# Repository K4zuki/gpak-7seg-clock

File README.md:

# gpak-7seg-clock
7-seg LED clock application using GreenPAK

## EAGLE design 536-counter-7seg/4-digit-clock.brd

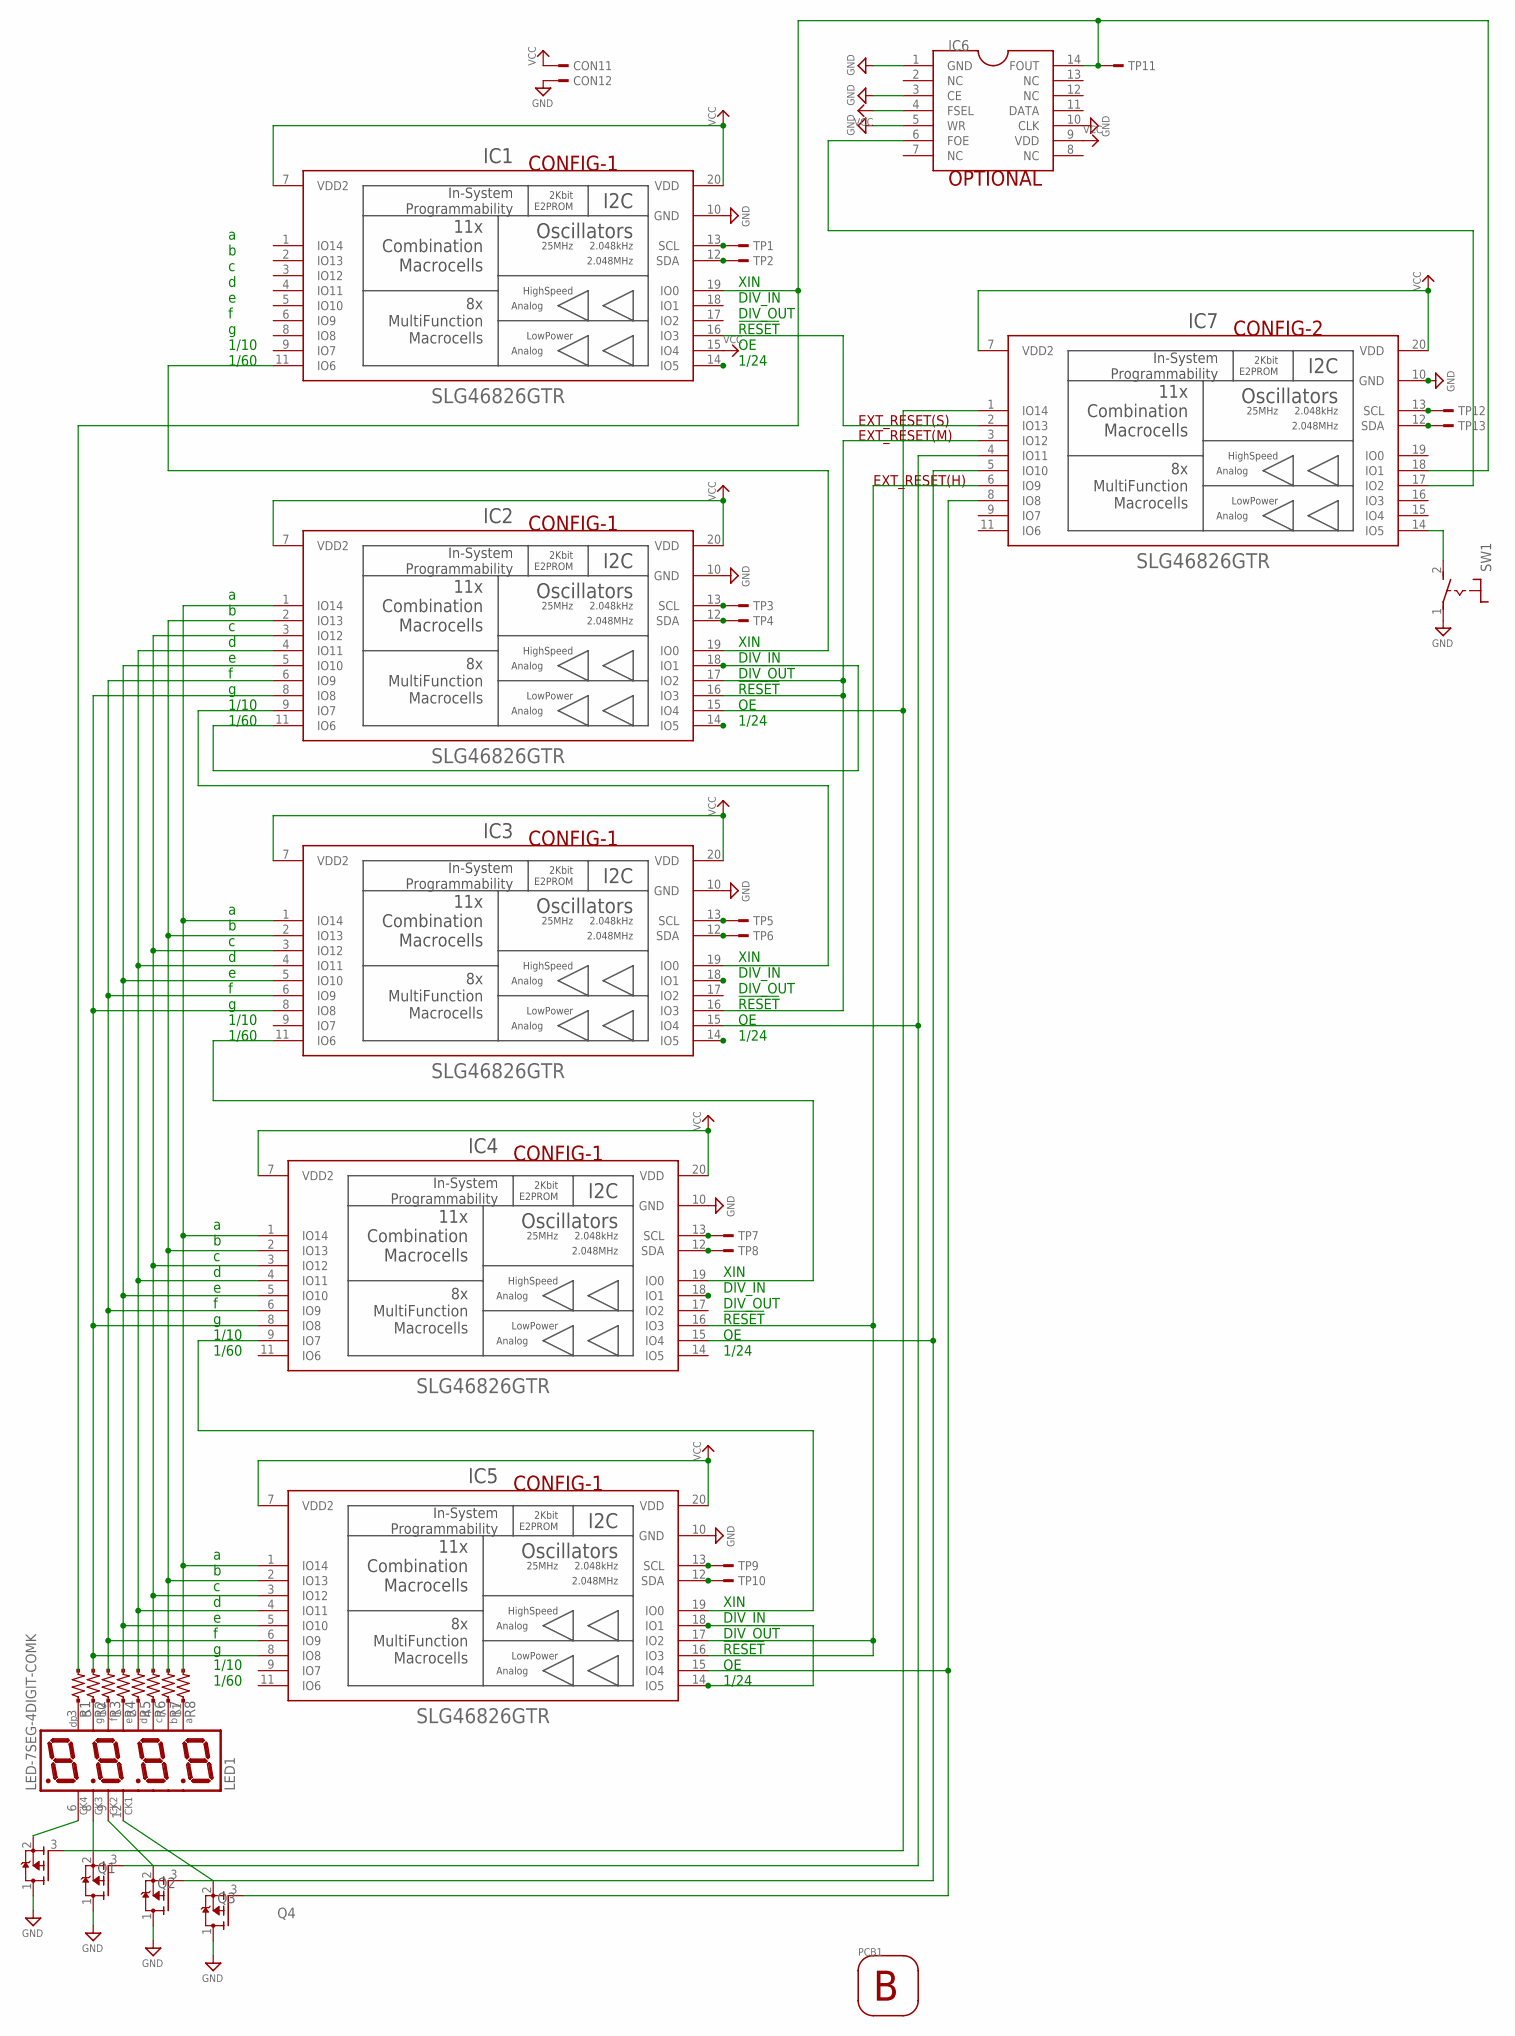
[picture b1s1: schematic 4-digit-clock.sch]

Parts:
CON1: B2B-XH-A; B2B-XH-A(LF)(SN)
IC1, IC2, IC3, IC4, IC5, IC7: SLG46826GTR; SOT65P650X440-20N
IC6: RTC-4543SA; SOT127P1010X500-14N
LED1: LED-7SEG-4DIGIT-COMK; LED-7SEG-4DIGIT
PCB1: P-MCS78A
Q1, Q2, Q3, Q4: 2N7002; SOT95P300X140-3N
R1, R2, R3, R4, R5, R6, R7, R8: R-US-1.0K-1005; C0402
SW1: TACTSW2-BK-TL1105S; SW-TACTSW-TL1105S
TP1, TP2, TP3, TP4, TP5, TP6, TP7, TP8, TP9, TP10, TP11, TP12, TP13: TESTPAD-1608; TP-1608

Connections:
GND: CON1.2, IC1.10 (GND), IC2.10 (GND), IC3.10 (GND), IC4.10 (GND), IC5.10 (GND), IC6.1 (GND), IC6.3 (CE), IC6.5 (WR), IC6.10 (CLK), IC7.10 (GND), Q1.1 (D), Q2.1 (D), Q3.1 (D), Q4.1 (D), SW1.1
unnamed: IC2.6 (IO9), IC3.6 (IO9), IC4.6 (IO9), IC5.6 (IO9), R3.2
unnamed: IC2.4 (IO11), IC3.4 (IO11), IC4.4 (IO11), IC5.4 (IO11), R5.2
unnamed: IC2.2 (IO13), IC3.2 (IO13), IC4.2 (IO13), IC5.2 (IO13), R7.2
unnamed: IC2.1 (IO14), IC3.1 (IO14), IC4.1 (IO14), IC5.1 (IO14), R8.2
unnamed: IC2.3 (IO12), IC3.3 (IO12), IC4.3 (IO12), IC5.3 (IO12), R6.2
unnamed: IC2.5 (IO10), IC3.5 (IO10), IC4.5 (IO10), IC5.5 (IO10), R4.2
unnamed: IC2.8 (IO8), IC3.8 (IO8), IC4.8 (IO8), IC5.8 (IO8), R2.2
unnamed: LED1.6 (CA4), Q1.2 (S)
unnamed: IC1.11 (IO6), IC2.19 (IO0)
unnamed: IC1.19 (IO0), IC6.14 (FOUT), IC7.18 (IO1), R1.2, TP11.TP
unnamed: IC2.11 (IO6), IC2.18 (IO1)
unnamed: LED1.8 (CA), Q2.2 (S)
unnamed: LED1.9 (CA), Q3.2 (S)
unnamed: LED1.12 (CA), Q4.2 (S)
unnamed: IC2.15 (IO4), IC7.1 (IO14), Q1.3 (G)
unnamed: IC3.15 (IO4), IC7.4 (IO11), Q2.3 (G)
unnamed: IC4.15 (IO4), IC7.5 (IO10), Q3.3 (G)
unnamed: IC2.9 (IO7), IC3.19 (IO0)
unnamed: IC5.15 (IO4), IC7.8 (IO8), Q4.3 (G)
unnamed: LED1.3 (DP), R1.1
unnamed: IC2.16 (IO3), IC2.17 (IO2), IC3.16 (IO3), IC7.3 (IO12)
unnamed: IC4.16 (IO3), IC5.16 (IO3), IC5.17 (IO2), IC7.6 (IO9)
unnamed: IC3.11 (IO6), IC4.19 (IO0)
unnamed: IC2.13 (SCL), TP3.TP
unnamed: IC2.12 (SDA), TP4.TP
unnamed: IC3.13 (SCL), TP5.TP
unnamed: IC3.12 (SDA), TP6.TP
unnamed: IC4.13 (SCL), TP7.TP
unnamed: IC4.12 (SDA), TP8.TP
unnamed: IC5.13 (SCL), TP9.TP
unnamed: IC5.14 (IO5), IC5.18 (IO1)
unnamed: LED1.5 (G), R2.1
unnamed: IC4.9 (IO7), IC5.19 (IO0)
unnamed: IC5.12 (SDA), TP10.TP
unnamed: LED1.10 (F), R3.1
unnamed: LED1.1 (E), R4.1
unnamed: LED1.2 (D), R5.1
unnamed: LED1.4 (C), R6.1
unnamed: LED1.7 (B), R7.1
unnamed: LED1.11 (A), R8.1
unnamed: IC7.13 (SCL), TP12.TP
unnamed: IC7.12 (SDA), TP13.TP
unnamed: IC7.14 (IO5), SW1.2 (S)
unnamed: IC6.6 (FOE), IC7.17 (IO2)
unnamed: IC1.16 (IO3), IC7.2 (IO13)
unnamed: IC1.13 (SCL), TP1.TP
unnamed: IC1.12 (SDA), TP2.TP
VCC: CON1.1, IC1.7 (VDD2), IC1.15 (IO4), IC1.20 (VDD), IC2.7 (VDD2), IC2.20 (VDD), IC3.7 (VDD2), IC3.20 (VDD), IC4.7 (VDD2), IC4.20 (VDD), IC5.7 (VDD2), IC5.20 (VDD), IC6.4 (FSEL), IC6.9 (VDD), IC7.7 (VDD2), IC7.20 (VDD)

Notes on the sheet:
XIN DIV_IN DIV_OUT !RESET! OE 1/24
a b c d e f g 1/10 1/60
CONFIG-1
CONFIG-2
OPTIONAL
EXT_RESET(S)
EXT_RESET(M)
EXT_RESET(H)

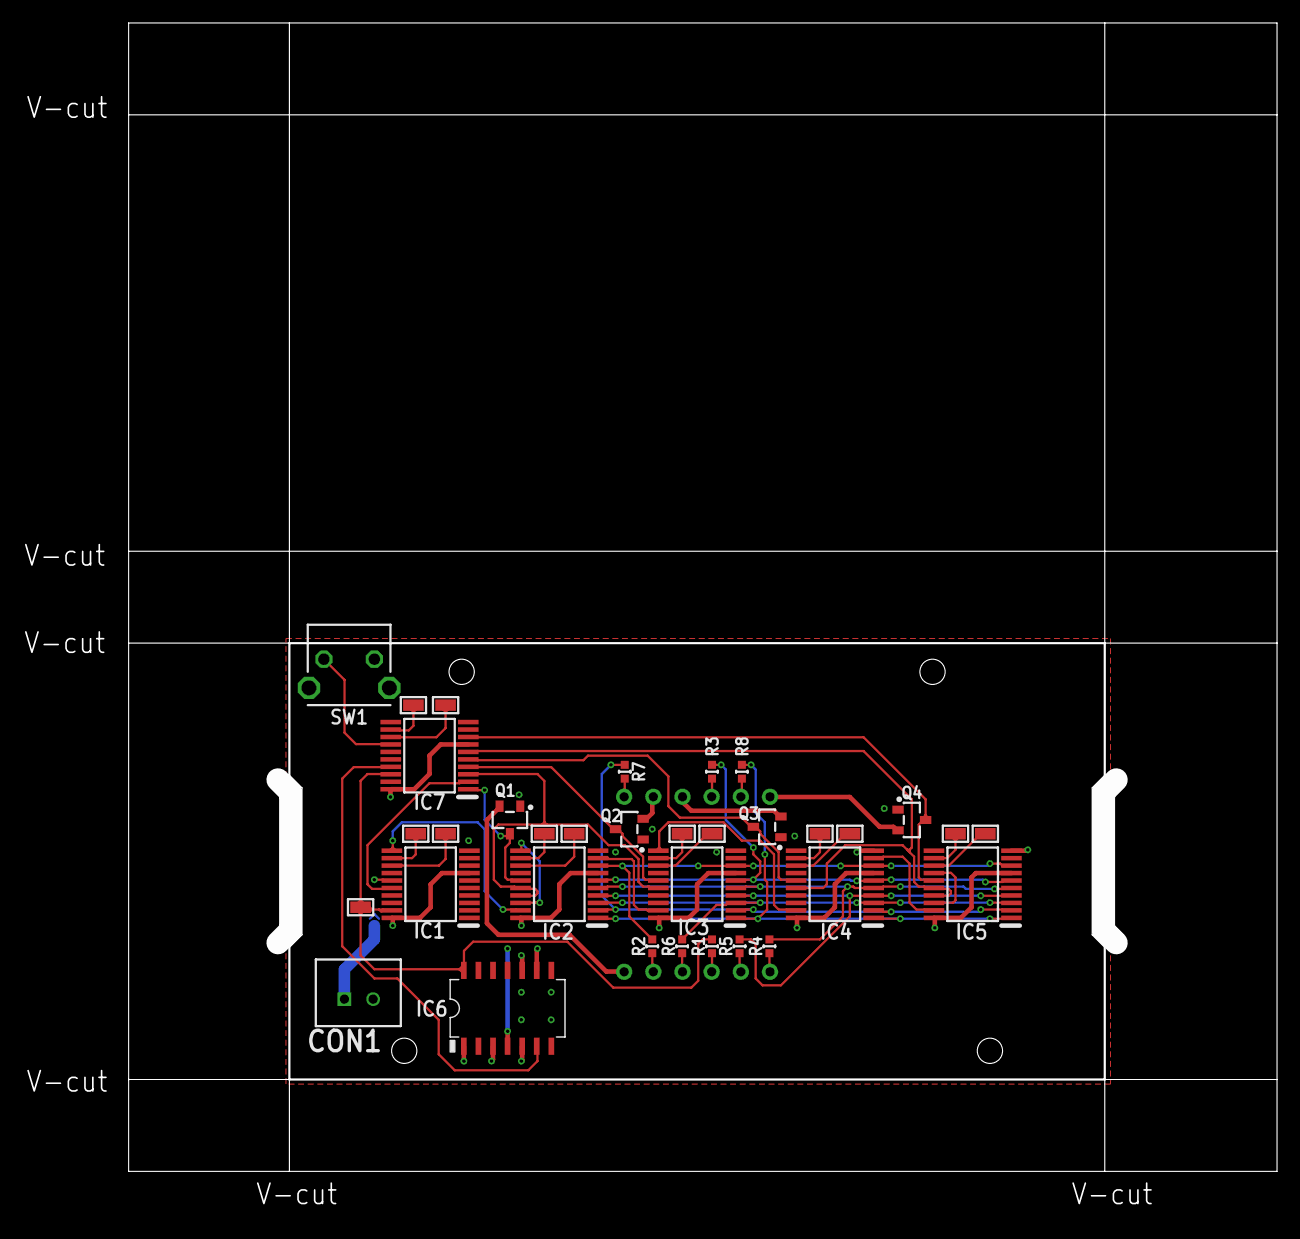
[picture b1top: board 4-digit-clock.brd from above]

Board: 2 copper layers, 107.2 x 101.9 mm, 36 parts (1 on the bottom side), 49 nets.

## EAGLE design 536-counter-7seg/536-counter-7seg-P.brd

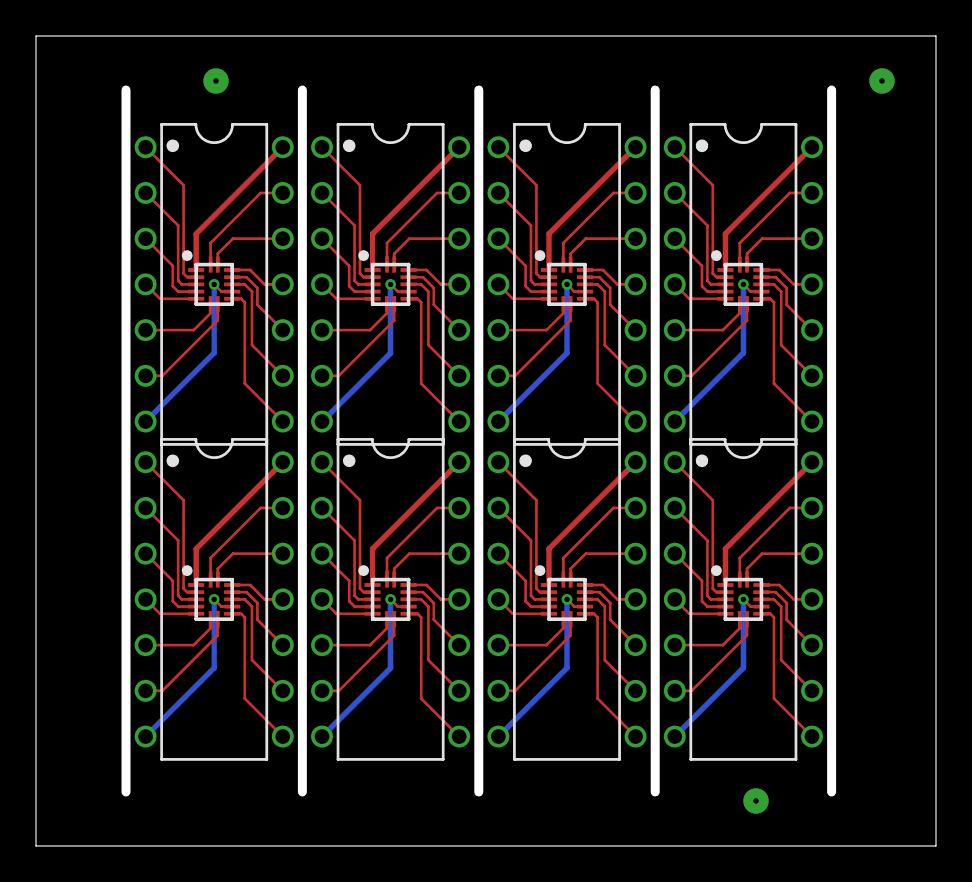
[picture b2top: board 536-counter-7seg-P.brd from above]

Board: 2 copper layers, 49.5 x 44.5 mm, 16 parts (0 on the bottom side), 112 nets.

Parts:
IC1, IC3, IC5, IC7, IC9, IC11, IC13, IC15: STQFN14-0.4P2.0X2.2
IC2, IC4, IC6, IC8, IC10, IC12, IC14, IC16: IC-TTL-74-04,14-DIP; IC-SOCKET-DIL-14

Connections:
GND: IC1.9, IC2.7
GND1: IC3.9, IC4.7
GND2: IC5.9, IC6.7
GND3: IC7.9, IC8.7
GND4: IC9.9, IC10.7
GND5: IC11.9, IC12.7
GND6: IC13.9, IC14.7
GND7: IC15.9, IC16.7
unnamed: IC1.1, IC2.14
unnamed: IC1.2, IC2.1
unnamed: IC1.3, IC2.2
unnamed: IC1.4, IC2.3
unnamed: IC1.5, IC2.4
unnamed: IC1.6, IC2.5
unnamed: IC1.7, IC2.6
unnamed: IC1.8, IC2.8
unnamed: IC1.10, IC2.9
unnamed: IC1.11, IC2.10
unnamed: IC1.12, IC2.11
unnamed: IC1.13, IC2.12
unnamed: IC1.14, IC2.13
unnamed: IC3.1, IC4.14
unnamed: IC3.2, IC4.1
unnamed: IC3.3, IC4.2
unnamed: IC3.4, IC4.3
unnamed: IC3.5, IC4.4
unnamed: IC3.6, IC4.5
unnamed: IC3.7, IC4.6
unnamed: IC3.8, IC4.8
unnamed: IC3.10, IC4.9
unnamed: IC3.11, IC4.10
unnamed: IC3.12, IC4.11
unnamed: IC3.13, IC4.12
unnamed: IC3.14, IC4.13
unnamed: IC5.1, IC6.14
unnamed: IC5.2, IC6.1
unnamed: IC5.3, IC6.2
unnamed: IC5.4, IC6.3
unnamed: IC5.5, IC6.4
unnamed: IC5.6, IC6.5
unnamed: IC5.7, IC6.6
unnamed: IC5.8, IC6.8
unnamed: IC5.10, IC6.9
unnamed: IC5.11, IC6.10
unnamed: IC5.12, IC6.11
unnamed: IC5.13, IC6.12
unnamed: IC5.14, IC6.13
unnamed: IC7.1, IC8.14
unnamed: IC7.2, IC8.1
unnamed: IC7.3, IC8.2
unnamed: IC7.4, IC8.3
unnamed: IC7.5, IC8.4
unnamed: IC7.6, IC8.5
unnamed: IC7.7, IC8.6
unnamed: IC7.8, IC8.8
unnamed: IC7.10, IC8.9
unnamed: IC7.11, IC8.10
unnamed: IC7.12, IC8.11
unnamed: IC7.13, IC8.12
unnamed: IC7.14, IC8.13
unnamed: IC9.1, IC10.14
unnamed: IC9.2, IC10.1
unnamed: IC9.3, IC10.2
unnamed: IC9.4, IC10.3
unnamed: IC9.5, IC10.4
unnamed: IC9.6, IC10.5
unnamed: IC9.7, IC10.6
unnamed: IC9.8, IC10.8
unnamed: IC9.10, IC10.9
unnamed: IC9.11, IC10.10
unnamed: IC9.12, IC10.11
unnamed: IC9.13, IC10.12
unnamed: IC9.14, IC10.13
unnamed: IC11.1, IC12.14
unnamed: IC11.2, IC12.1
unnamed: IC11.3, IC12.2
unnamed: IC11.4, IC12.3
unnamed: IC11.5, IC12.4
unnamed: IC11.6, IC12.5
unnamed: IC11.7, IC12.6
unnamed: IC11.8, IC12.8
unnamed: IC11.10, IC12.9
unnamed: IC11.11, IC12.10
unnamed: IC11.12, IC12.11
unnamed: IC11.13, IC12.12
unnamed: IC11.14, IC12.13
unnamed: IC13.1, IC14.14
unnamed: IC13.2, IC14.1
unnamed: IC13.3, IC14.2
unnamed: IC13.4, IC14.3
unnamed: IC13.5, IC14.4
unnamed: IC13.6, IC14.5
unnamed: IC13.7, IC14.6
unnamed: IC13.8, IC14.8
unnamed: IC13.10, IC14.9
unnamed: IC13.11, IC14.10
unnamed: IC13.12, IC14.11
unnamed: IC13.13, IC14.12
unnamed: IC13.14, IC14.13
unnamed: IC15.1, IC16.14
unnamed: IC15.2, IC16.1
unnamed: IC15.3, IC16.2
unnamed: IC15.4, IC16.3
unnamed: IC15.5, IC16.4
unnamed: IC15.6, IC16.5
unnamed: IC15.7, IC16.6
unnamed: IC15.8, IC16.8
unnamed: IC15.10, IC16.9
unnamed: IC15.11, IC16.10
unnamed: IC15.12, IC16.11
unnamed: IC15.13, IC16.12
unnamed: IC15.14, IC16.13

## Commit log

2019-08-14 add gpak files; add gitignore
2019-08-14 add board files
2019-08-14 add document files
2019-08-17 initial inputs
2019-08-18 add overview block diagram
2019-08-21 update counter-7seg gp files
2019-08-21 update block diagram
2019-08-21 add ring shifter gpak files
2020-04-11 update schematics
    - bcd-counter-7seg.gp6 = 46826 segment decoder/counter
    - ring-shifter.gp6 = 46826 digit shifter/switch interface
    - 536-* = for 46536 although target schematic does not fit
2020-04-11 add 4-digit clock application schematic and board layout
2020-04-28 update pcb layouts
2020-05-02 update gp6 schematics
2020-05-02 update document
2020-05-03 update GP6 schematic
2020-06-03 add block-diagram-2.bob
2020-09-24 add QRcode.png
2020-09-24 add MilkyWay_Stargate_blank.svg
2020-09-24 update config.yaml - update subtitle; change front image; add frontoption metadata entry
2020-09-24 update TITLE.md
    - add front image
    - add tailnote and thanks
2020-09-28 update block-diagram-2.bob - add RTC
2021-01-03 add clock-divider-block.png
2021-01-03 update TITLE.md - add statements about clock divider block
2021-01-03 update TITLE.md - add configuration tables for each macrocell
2021-01-04 update block-diagram-2.bob - removed digC signal, rename from l1l2 to l12
2021-01-04 update truth-table.csv - add decimal number column
2021-01-05 update TITLE.md - add PIN2 and PIN3 config tables; update column ratio
2021-01-26 update TITLE.md; add counter block images
    - update front section to explain Chevron, and how 7 comes
    - update MF7 configuration table
    - update counter block sections
    - shrink QR code image size
2021-02-28 update TITLE.md, add pictures
2021-11-22 add multiple screenshots
2022-05-12 update Dockerfile - drop tlmgr update for now
2024-06-20 update config.yaml - setup docx config
2024-06-20 add frontpage.md
2024-06-20 update TITLE.md - hard wrap
2024-06-20 update Makefile - use local front page file
2024-06-20 add mux diagram files
